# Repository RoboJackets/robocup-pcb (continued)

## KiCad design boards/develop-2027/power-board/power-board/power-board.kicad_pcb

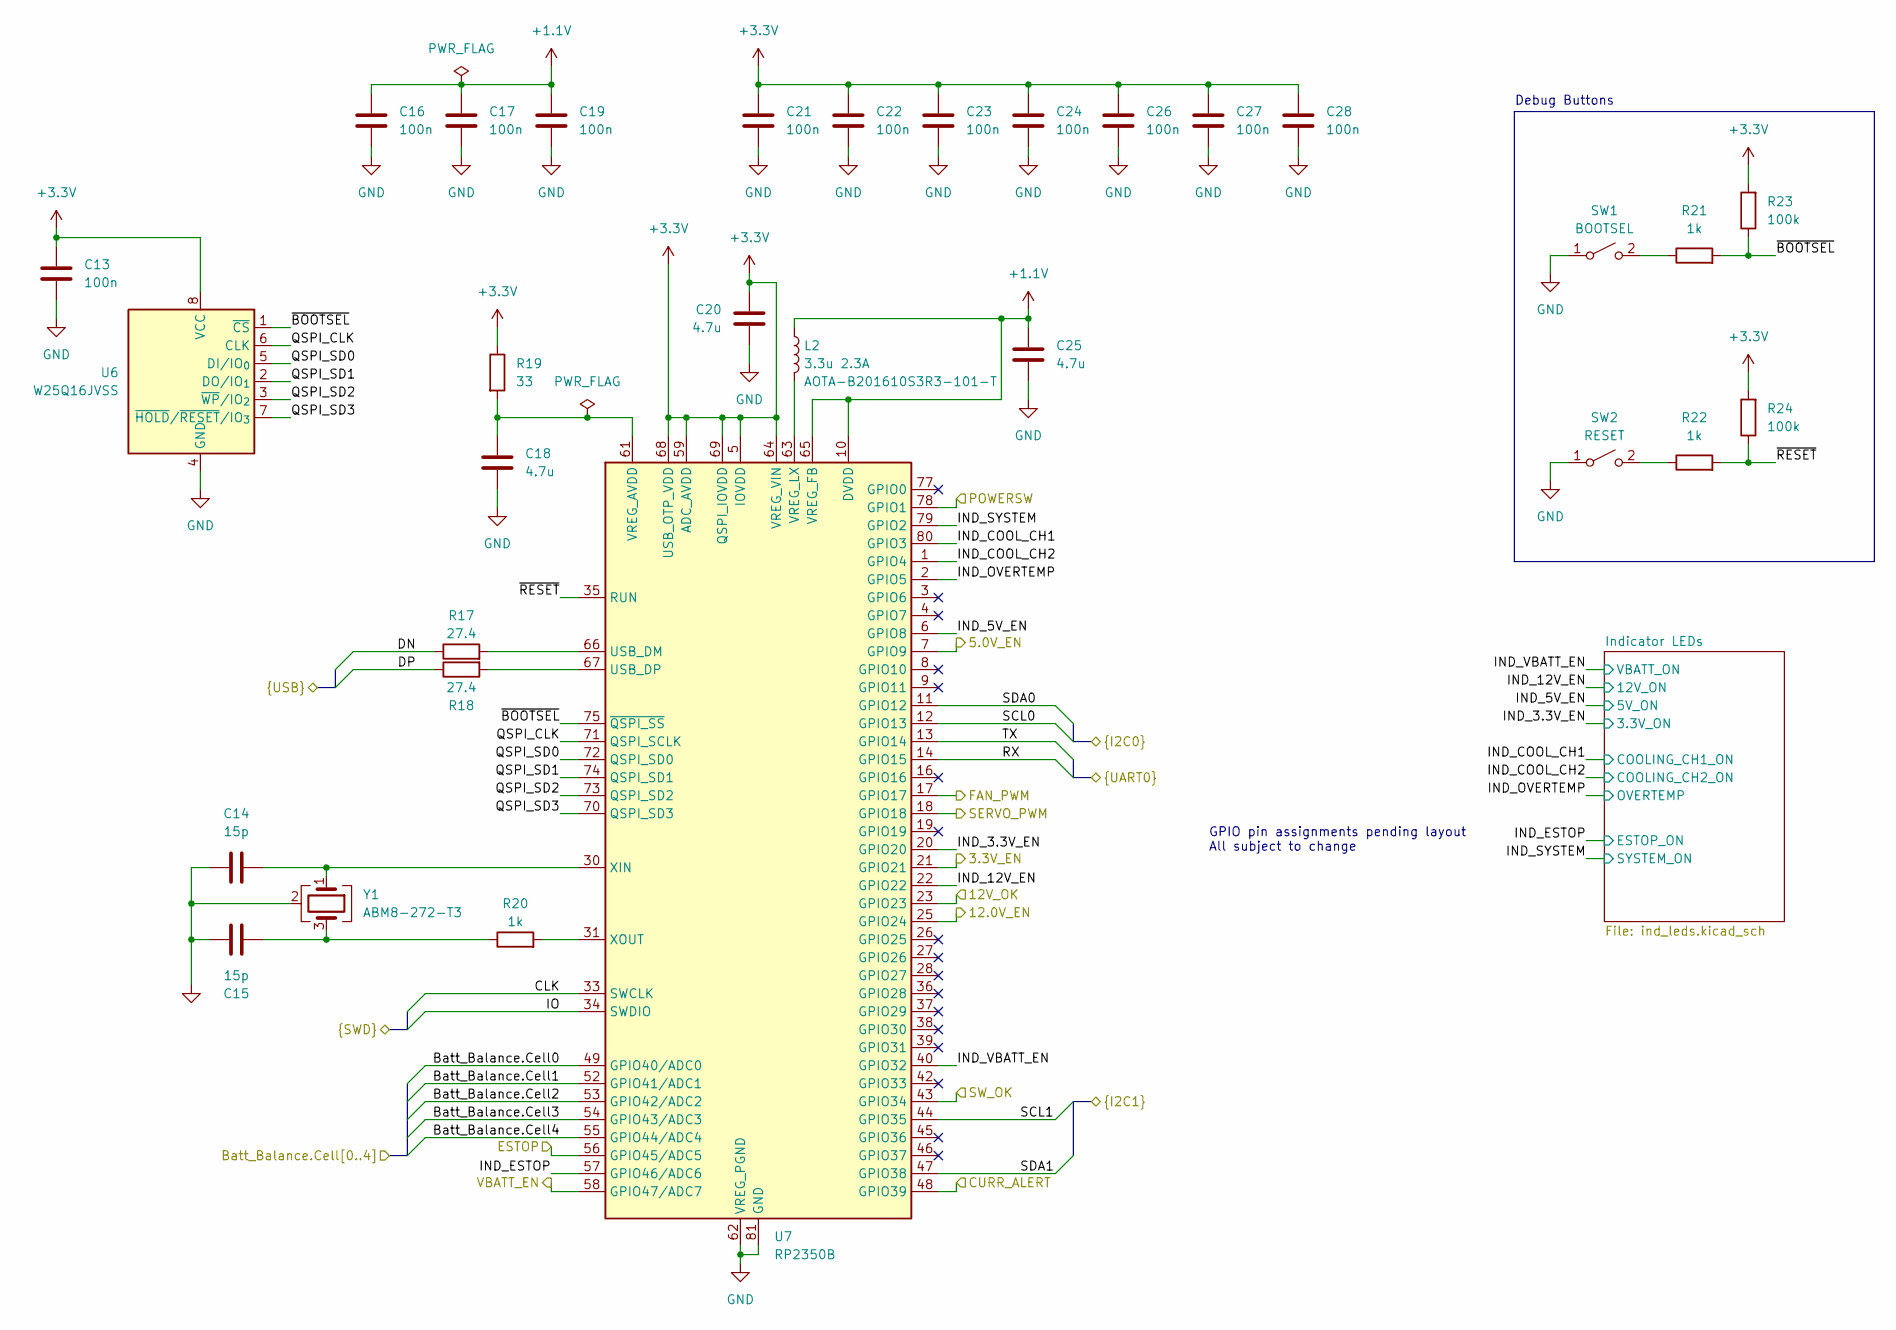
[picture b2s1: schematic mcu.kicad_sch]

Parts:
C13, C16, C17, C19, C21, C22, C23, C24, C26, C27, C28: 100n; C_0402_1005Metric; Manufacturer P/N GCM155R71H104KE02D
C14, C15: 15p; C_0402_1005Metric; Manufacturer P/N GJM1555C1H150GB01D
C18, C20, C25: 4.7u; C_0402_1005Metric; Manufacturer P/N GRM155R60J475ME47D
L2: 3.3u 2.3A; L_Abracon_AOTA-B201610S; Manufacturer P/N AOTA-B201610S3R3-101-T
R17, R18: 27.4; R_0402_1005Metric; Manufacturer P/N RC0402FR-0727R4L
R19: 33; R_0402_1005Metric; Manufacturer P/N RC0402JR-0733RL
R20, R21, R22: 1k; R_0402_1005Metric; Manufacturer P/N RC0402FR-071KL
R23, R24: 100k; R_0402_1005Metric; Manufacturer P/N RC0402FR-07100KL
SW1: BOOTSEL; SW_Push_1P1T_NO_CK_KMR2; Manufacturer P/N KMR211G LFS
SW2: RESET; SW_Push_1P1T_NO_CK_KMR2; Manufacturer P/N KMR211G LFS
U6: W25Q16JVSS; SOIC-8_5.3x5.3mm_P1.27mm; Manufacturer P/N W25Q16JVSSIQ
U7: RP2350B; QFN-80-1EP_10x10mm_P0.4mm_EP3.4x3.4mm; Manufacturer P/N RP2350B
Y1: ABM8-272-T3; Crystal_SMD_Abracon_ABM8G-4Pin_3.2x2.5mm; Manufacturer P/N ABM8-272-T3

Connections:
+1.1V: C16.1, C17.1, C19.1, C25.1, L2.1, U7.10 (DVDD), U7.32 (DVDD), U7.51 (DVDD), U7.65 (VREG_FB)
+3.3V: C13.1, C20.1, C21.1, C22.1, C23.1, C24.1, C26.1, C27.1, C28.1, R19.1, R23.2, R24.2, U6.8 (VCC), U7.5 (IOVDD), U7.15 (IOVDD), U7.24 (IOVDD), U7.29 (IOVDD), U7.41 (IOVDD), U7.50 (IOVDD), U7.59 (ADC_AVDD), U7.60 (IOVDD), U7.64 (VREG_VIN), U7.68 (USB_OTP_VDD), U7.69 (QSPI_IOVDD), U7.76 (IOVDD); also elsewhere on the board
/Battery Connectors/Batt_Balance.Cell0: U7.49 (GPIO40/ADC0); also elsewhere on the board
/Battery Connectors/Batt_Balance.Cell1: U7.52 (GPIO41/ADC1); also elsewhere on the board
/Battery Connectors/Batt_Balance.Cell2: U7.53 (GPIO42/ADC2); also elsewhere on the board
/Battery Connectors/Batt_Balance.Cell3: U7.54 (GPIO43/ADC3); also elsewhere on the board
/Battery Connectors/Batt_Balance.Cell4: U7.55 (GPIO44/ADC4); also elsewhere on the board
/MCU Connectors/CLK: U7.33 (SWCLK); also elsewhere on the board
/MCU Connectors/DN: R17.1; also elsewhere on the board
/MCU Connectors/DP: R18.1; also elsewhere on the board
/MCU Connectors/IO: U7.34 (SWDIO); also elsewhere on the board
/MCU/3.3V_EN: U7.21 (GPIO21); also elsewhere on the board
/MCU/5.0V_EN: U7.7 (GPIO9); also elsewhere on the board
/MCU/12.0V_EN: U7.25 (GPIO24); also elsewhere on the board
/MCU/12V_OK: U7.23 (GPIO23); also elsewhere on the board
/MCU/CURR_ALERT: U7.48 (GPIO39); also elsewhere on the board
/MCU/ESTOP: U7.56 (GPIO45/ADC5); also elsewhere on the board
/MCU/FAN_PWM: U7.17 (GPIO17); also elsewhere on the board
/MCU/IND_3.3V_EN: U7.20 (GPIO20); also elsewhere on the board
/MCU/IND_5V_EN: U7.6 (GPIO8); also elsewhere on the board
/MCU/IND_12V_EN: U7.22 (GPIO22); also elsewhere on the board
/MCU/IND_COOL_CH1: U7.80 (GPIO3); also elsewhere on the board
/MCU/IND_COOL_CH2: U7.1 (GPIO4); also elsewhere on the board
/MCU/IND_ESTOP: U7.57 (GPIO46/ADC6); also elsewhere on the board
/MCU/IND_OVERTEMP: U7.2 (GPIO5); also elsewhere on the board
/MCU/IND_SYSTEM: U7.79 (GPIO2); also elsewhere on the board
/MCU/IND_VBATT_EN: U7.40 (GPIO32); also elsewhere on the board
/MCU/POWERSW: U7.78 (GPIO1); also elsewhere on the board
/MCU/QSPI_CLK: U6.6 (CLK), U7.71 (QSPI_SCLK)
/MCU/QSPI_SD0: U6.5 (DI/IO_{0}), U7.72 (QSPI_SD0)
/MCU/QSPI_SD1: U6.2 (DO/IO_{1}), U7.74 (QSPI_SD1)
/MCU/QSPI_SD2: U6.3 (~WP/IO_{2}), U7.73 (QSPI_SD2)
/MCU/QSPI_SD3: U6.7 (~HOLD/~RESET/IO_{3}), U7.70 (QSPI_SD3)
/MCU/RX: U7.14 (GPIO15); also elsewhere on the board
/MCU/SCL0: U7.12 (GPIO13); also elsewhere on the board
/MCU/SCL1: U7.44 (GPIO35); also elsewhere on the board
/MCU/SDA0: U7.11 (GPIO12); also elsewhere on the board
/MCU/SDA1: U7.47 (GPIO38); also elsewhere on the board
/MCU/SERVO_PWM: U7.18 (GPIO18); also elsewhere on the board
/MCU/SW_OK: U7.43 (GPIO34); also elsewhere on the board
/MCU/TX: U7.13 (GPIO14); also elsewhere on the board
/MCU/VBATT_EN: U7.58 (GPIO47/ADC7); also elsewhere on the board
/MCU/~BOOTSEL: R21.2, R23.1, U6.1 (~CS), U7.75 (~QSPI_SS)
/MCU/~RESET: R22.2, R24.1, U7.35 (RUN)
GND: C13.2, C14.1, C15.1, C16.2, C17.2, C18.2, C19.2, C20.2, C21.2, C22.2, C23.2, C24.2, C25.2, C26.2, C27.2, C28.2, SW1.1 (A), SW2.1 (A), U6.4 (GND), U7.62 (VREG_PGND), U7.81 (GND), Y1.2 (G), Y1.4 (G); also elsewhere on the board
unnamed: C15.2, R20.1, Y1.3
unnamed: R21.1, SW1.2 (B)
unnamed: R22.1, SW2.2 (B)
unnamed: R17.2, U7.66 (USB_DM)
unnamed: R18.2, U7.67 (USB_DP)
unnamed: C18.1, R19.2, U7.61 (VREG_AVDD)
unnamed: L2.2, U7.63 (VREG_LX)
unnamed: C14.2, U7.30 (XIN), Y1.1
unnamed: R20.2, U7.31 (XOUT)

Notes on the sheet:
GPIO pin assignments pending layout All subject to change
Debug Buttons

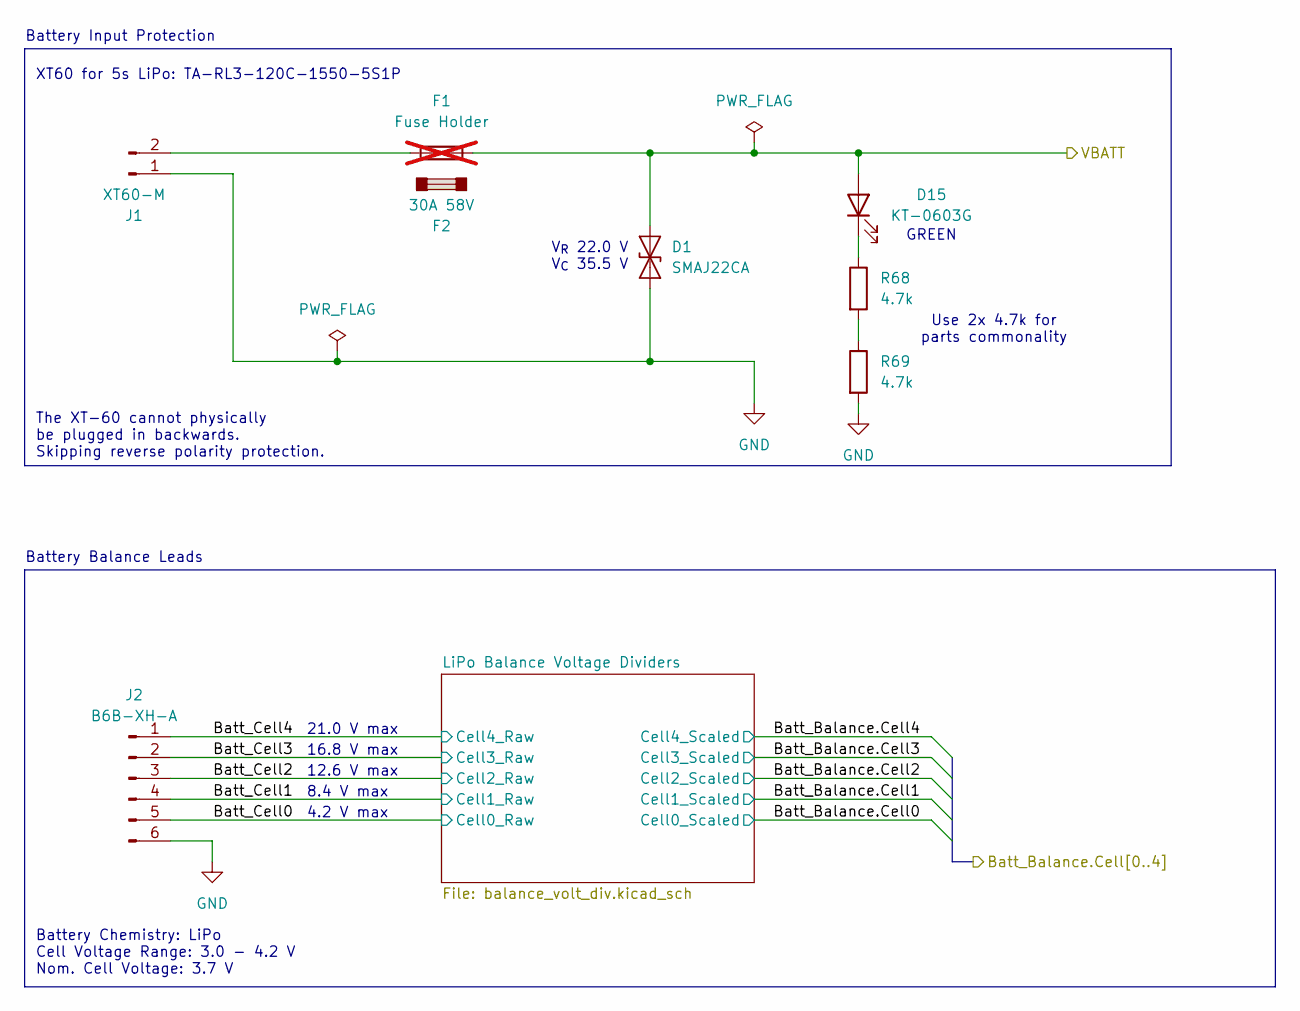
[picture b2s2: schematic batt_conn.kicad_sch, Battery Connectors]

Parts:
D1: SMAJ22CA; D_SMA; Manufacturer P/N SMAJ22CA
D15: KT-0603G; LED_0603_1608Metric; Manufacturer P/N KT-0603G
F1: Fuse Holder; Fuseholder_Keystone_3557-2; Manufacturer P/N 3557-2; not fitted
F2: 30A 58V; Manufacturer P/N 0891030.NXS
J1: XT60-M; AMASS_XT60-M_1x02_P7.20mm_Vertical; Manufacturer P/N XT60-M.
J2: B6B-XH-A; JST_XH_B6B-XH-A_1x06_P2.50mm_Vertical; Manufacturer P/N B6B-XH-A
R68, R69: 4.7k; R_0402_1005Metric; Manufacturer P/N RC0402FR-074K7L

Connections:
/Battery Connectors/Batt_Cell0: J2.5; also elsewhere on the board
/Battery Connectors/Batt_Cell1: J2.4; also elsewhere on the board
/Battery Connectors/Batt_Cell2: J2.3; also elsewhere on the board
/Battery Connectors/Batt_Cell3: J2.2; also elsewhere on the board
/Battery Connectors/Batt_Cell4: J2.1; also elsewhere on the board
/Battery Connectors/VBATT: D1.1 (A1), D15.2 (A), F1.2; also elsewhere on the board
GND: D1.2 (A2), J1.1, J2.6, R69.2; also elsewhere on the board
unnamed: D15.1 (K), R68.1
unnamed: F1.1, J1.2
unnamed: R68.2, R69.1

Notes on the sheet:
4.2 V max
Battery Balance Leads
21.0 V max
Use 2x 4.7k for parts commonality
XT60 for 5s LiPo: TA-RL3-120C-1550-5S1P
12.6 V max
V_{R} 22.0 V V_{C} 35.5 V
8.4 V max
16.8 V max
GREEN
The XT-60 cannot physically be plugged in backwards. Skipping reverse polarity protection.
Battery Input Protection
Battery Chemistry: LiPo Cell Voltage Range: 3.0 - 4.2 V Nom. Cell Voltage: 3.7 V

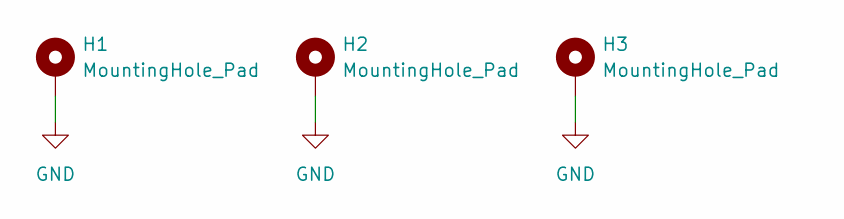
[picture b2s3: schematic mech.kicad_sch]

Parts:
H1, H2, H3: MountingHole_Pad; MountingHole_3.2mm_M3_Pad

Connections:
GND: H1.1 (1_1), H2.1 (1_1), H3.1 (1_1); also elsewhere on the board

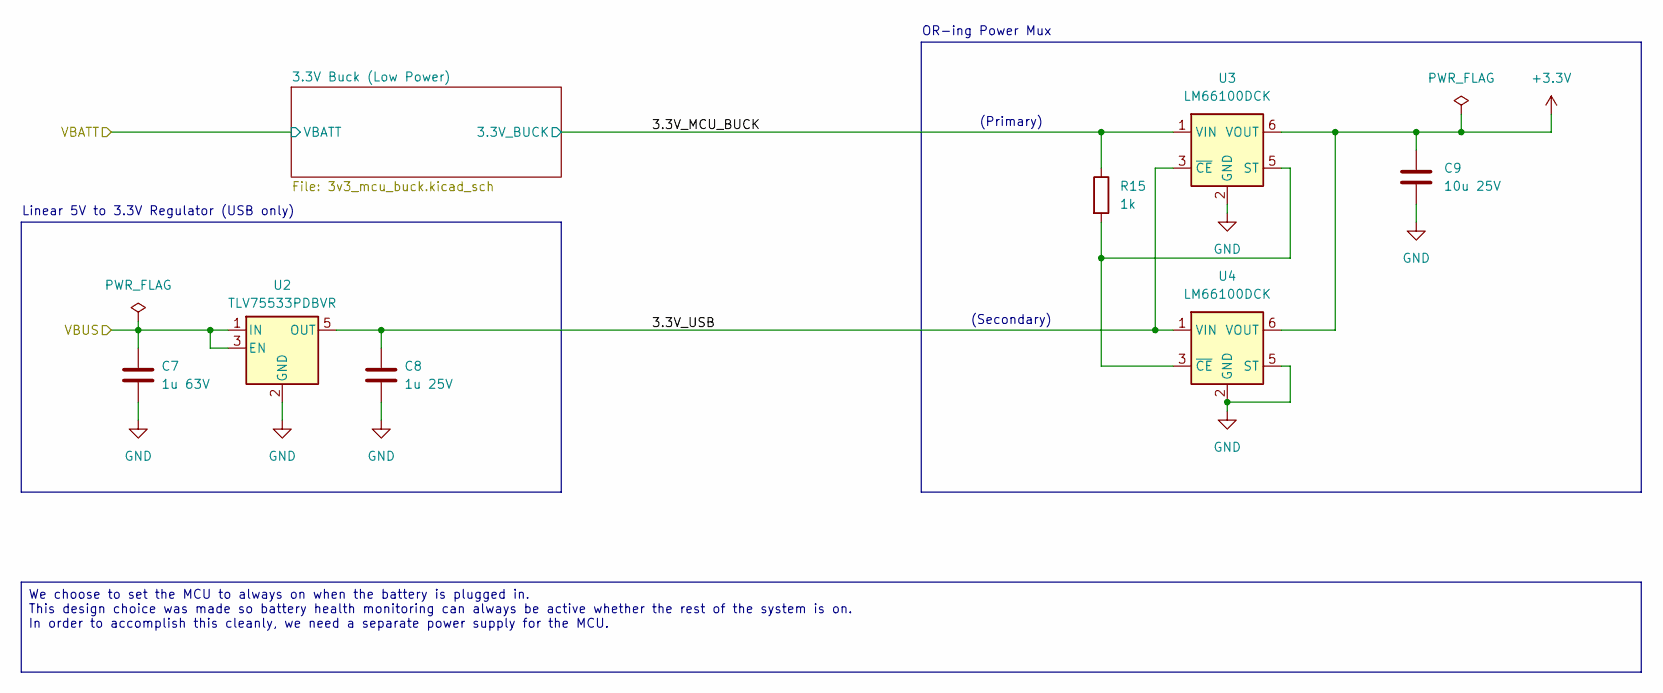
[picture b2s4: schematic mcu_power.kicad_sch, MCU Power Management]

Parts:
C7: 1u 63V; C_0603_1608Metric; Manufacturer P/N CL10B105KB8NQNC
C8: 1u 25V; C_0603_1608Metric; Manufacturer P/N CL10B105KB8NQNC
C9: 10u 25V; C_0603_1608Metric; Manufacturer P/N GRM188R6YA106MA73D
R15: 1k; R_0402_1005Metric; Manufacturer P/N RC0402FR-071KL
U2: TLV75533PDBVR; SOT-23-5; Manufacturer P/N TLV75533PDBVR
U3, U4: LM66100DCK; SOT-363_SC-70-6; Manufacturer P/N LM66100DCKR

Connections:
+3.3V: C9.1, U3.6 (VOUT), U4.6 (VOUT); also elsewhere on the board
/MCU Power/3.3V_MCU_BUCK: R15.1, U3.1 (VIN); also elsewhere on the board
/MCU Power/3.3V_USB: C8.1, U2.5 (OUT), U3.3 (~CE), U4.1 (VIN)
GND: C7.2, C8.2, C9.2, U2.2 (GND), U3.2 (GND), U4.2 (GND), U4.5 (ST); also elsewhere on the board
unnamed: R15.2, U3.5 (ST), U4.3 (~CE)
VBUS: C7.1, U2.1 (IN), U2.3 (EN); also elsewhere on the board

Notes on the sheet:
(Primary)
(Secondary)
Linear 5V to 3.3V Regulator (USB only)
OR-ing Power Mux
We choose to set the MCU to always on when the battery is plugged in. This design choice was made so battery health monitoring can always be active whether the rest of the system is on. In order to accomplish this cleanly, we need a separate power supply for the MCU.

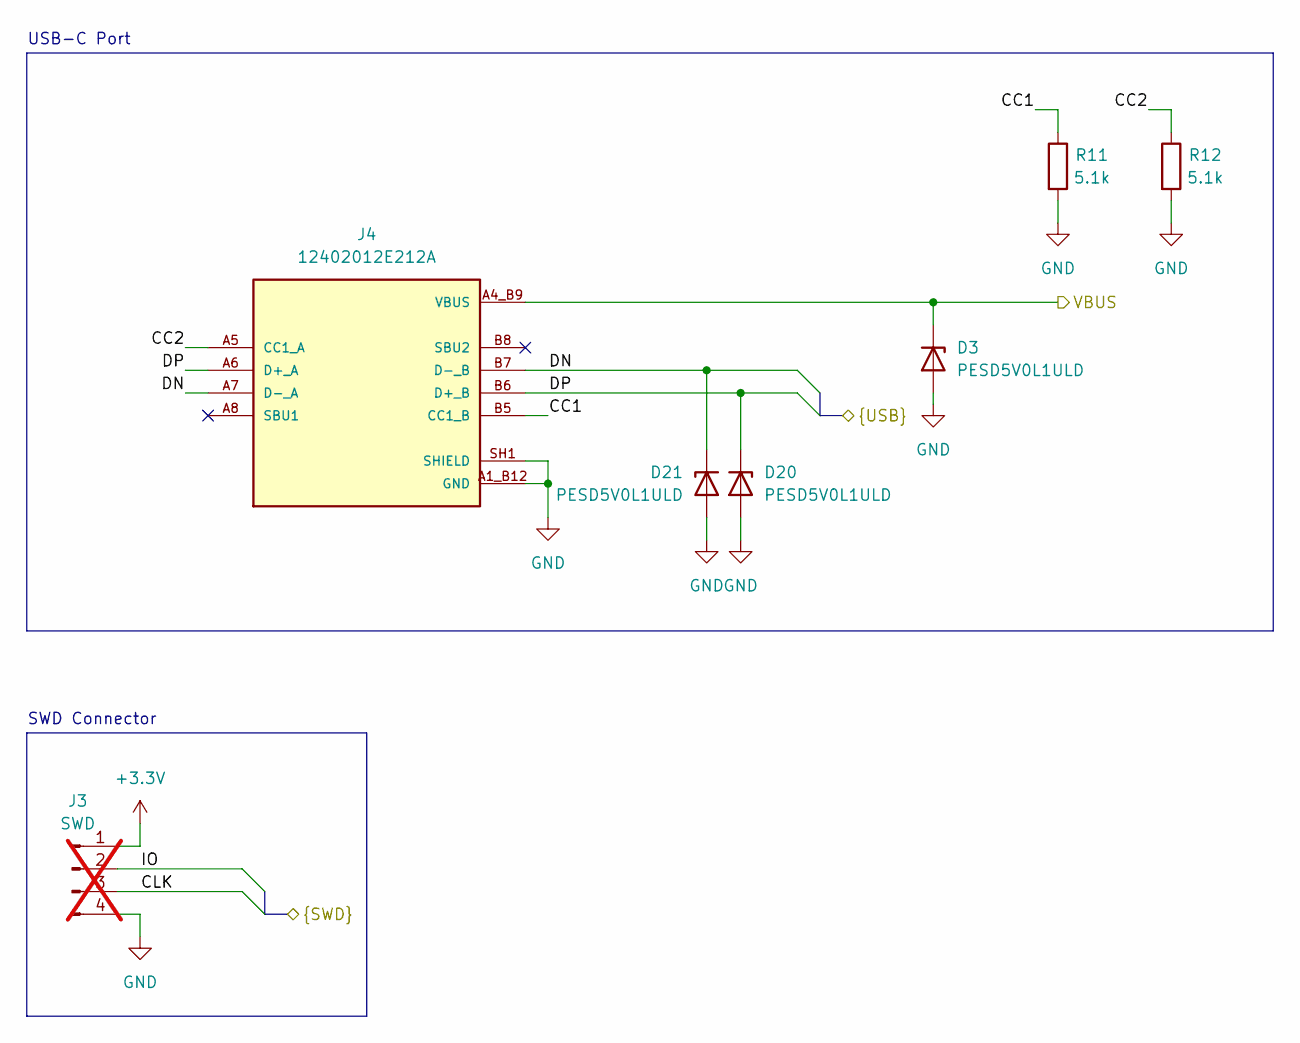
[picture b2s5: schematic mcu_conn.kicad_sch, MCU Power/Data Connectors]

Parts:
D3, D20, D21: PESD5V0L1ULD; D_SOD-882D; Manufacturer P/N PESD5V0H1BSFYL
J3: SWD; PinHeader_1x04_P2.54mm_Vertical; not fitted
J4: 12402012E212A; USB_C_Receptable_Amphenol_12402012E212A; Manufacturer P/N 12402012E212A
R11, R12: 5.1k; R_0402_1005Metric; Manufacturer P/N RC0402FR-075K1L

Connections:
+3.3V: J3.1; also elsewhere on the board
/MCU Connectors/CC1: J4.B5 (CC1_B), R11.1
/MCU Connectors/CC2: J4.A5 (CC1_A), R12.1
/MCU Connectors/CLK: J3.3; also elsewhere on the board
/MCU Connectors/DN: D21.1 (K), J4.A7 (D-_A), J4.B7 (D-_B); also elsewhere on the board
/MCU Connectors/DP: D20.1 (K), J4.A6 (D+_A), J4.B6 (D+_B); also elsewhere on the board
/MCU Connectors/IO: J3.2; also elsewhere on the board
GND: D3.2 (A), D20.2 (A), D21.2 (A), J3.4, J4.A1_B12 (GND), J4.B1_A12 (GND), J4.SH1 (SHIELD), J4.SH2 (SHIELD), J4.SH3 (SHIELD), J4.SH4 (SHIELD), R11.2, R12.2; also elsewhere on the board
VBUS: D3.1 (K), J4.A4_B9 (VBUS), J4.B4_A9 (VBUS); also elsewhere on the board

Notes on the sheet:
SWD Connector
USB-C Port

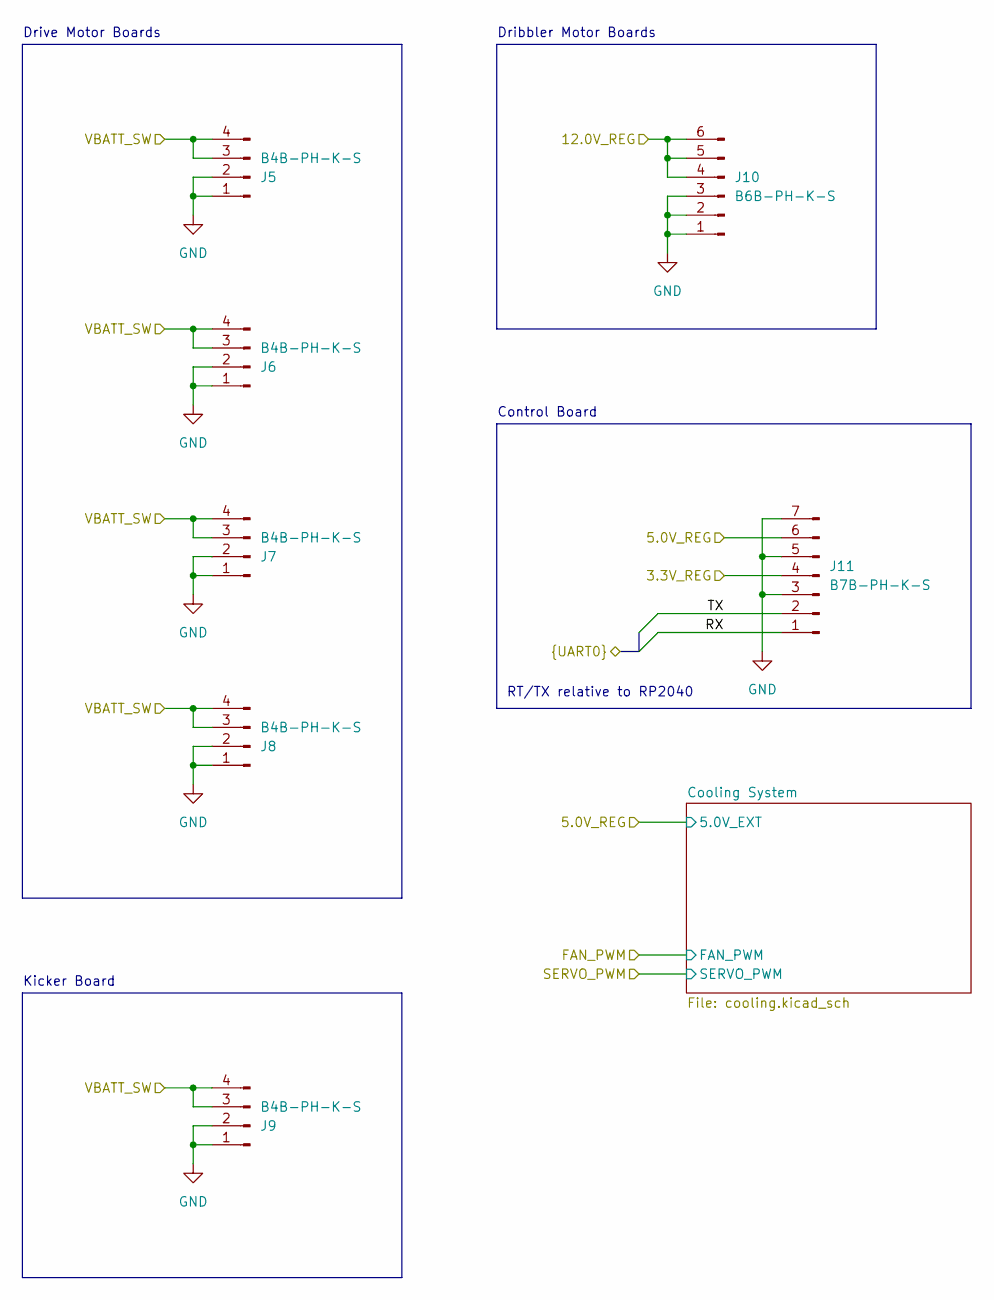
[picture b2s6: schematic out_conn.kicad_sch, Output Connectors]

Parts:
J5, J6, J7, J8, J9: B4B-PH-K-S; JST_PH_B4B-PH-K_1x04_P2.00mm_Vertical; Manufacturer P/N B4B-PH-K-S
J10: B6B-PH-K-S; JST_PH_B6B-PH-K_1x06_P2.00mm_Vertical; Manufacturer P/N B6B-PH-K-S
J11: B7B-PH-K-S; JST_PH_B7B-PH-K_1x07_P2.00mm_Vertical; Manufacturer P/N B7B-PH-K-S

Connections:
/MCU/RX: J11.1; also elsewhere on the board
/MCU/TX: J11.2; also elsewhere on the board
/Output Connectors/3.3V_REG: J11.4; also elsewhere on the board
/Output Connectors/5.0V_REG: J11.6; also elsewhere on the board
/Output Connectors/12.0V_REG: J10.4, J10.5, J10.6; also elsewhere on the board
GND: J5.1, J5.2, J6.1, J6.2, J7.1, J7.2, J8.1, J8.2, J9.1, J9.2, J10.1, J10.2, J10.3, J11.3, J11.5, J11.7; also elsewhere on the board
VIN: J5.3, J5.4, J6.3, J6.4, J7.3, J7.4, J8.3, J8.4, J9.3, J9.4; also elsewhere on the board

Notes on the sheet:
Drive Motor Boards
RT/TX relative to RP2040
Kicker Board
Control Board
Dribbler Motor Boards

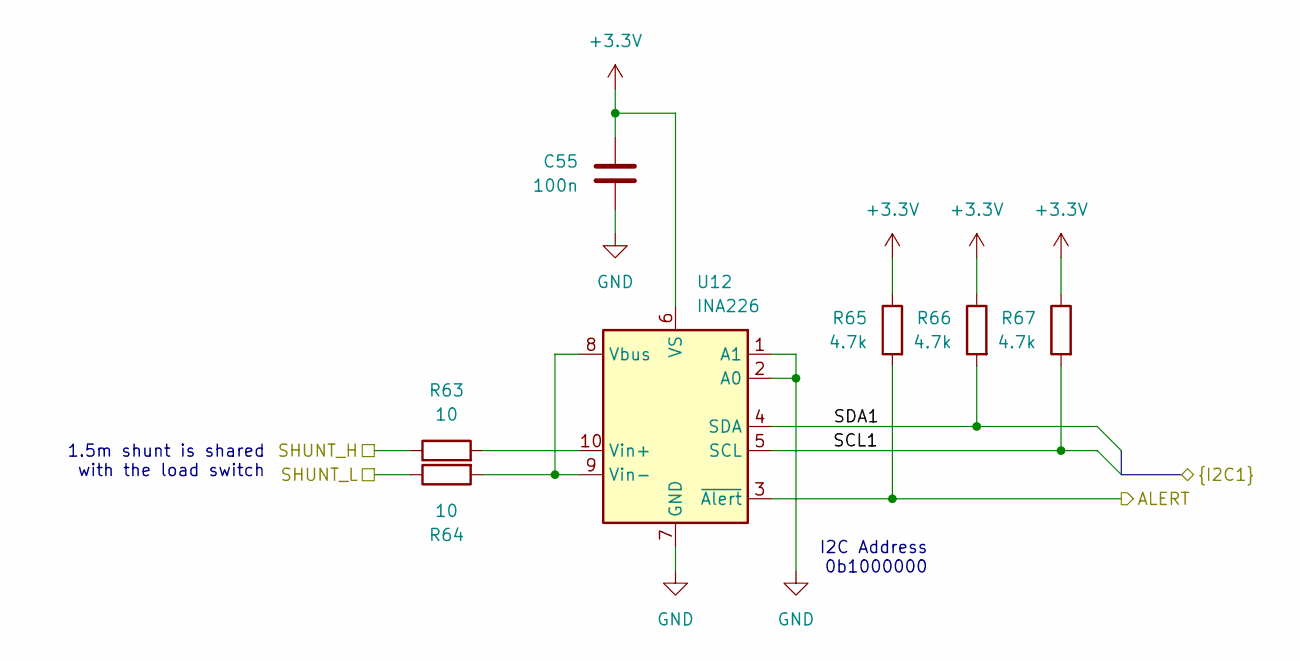
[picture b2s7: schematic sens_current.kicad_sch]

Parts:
C55: 100n; C_0402_1005Metric; Manufacturer P/N GCM155R71H104KE02D
R63, R64: 10; R_0402_1005Metric; Manufacturer P/N RC0402FR-0710RL
R65, R66, R67: 4.7k; R_0402_1005Metric; Manufacturer P/N RC0402FR-074K7L
U12: INA226; TSSOP-10_3x3mm_P0.5mm; Manufacturer P/N INA226AIDGSR

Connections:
+3.3V: C55.1, R65.1, R66.1, R67.1, U12.6 (VS); also elsewhere on the board
/MCU/CURR_ALERT: R65.2, U12.3 (~Alert); also elsewhere on the board
/MCU/SCL1: R67.2, U12.5 (SCL); also elsewhere on the board
/MCU/SDA1: R66.2, U12.4 (SDA); also elsewhere on the board
/Output Power Stage/25V, 30A Load Switch/SHUNT_H: R63.1; also elsewhere on the board
/Output Power Stage/25V, 30A Load Switch/SHUNT_L: R64.1; also elsewhere on the board
GND: C55.2, U12.1 (A1), U12.2 (A0), U12.7 (GND); also elsewhere on the board
unnamed: R64.2, U12.8 (Vbus), U12.9 (Vin-)
unnamed: R63.2, U12.10 (Vin+)

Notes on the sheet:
I2C Address 0b1000000
1.5m shunt is shared with the load switch

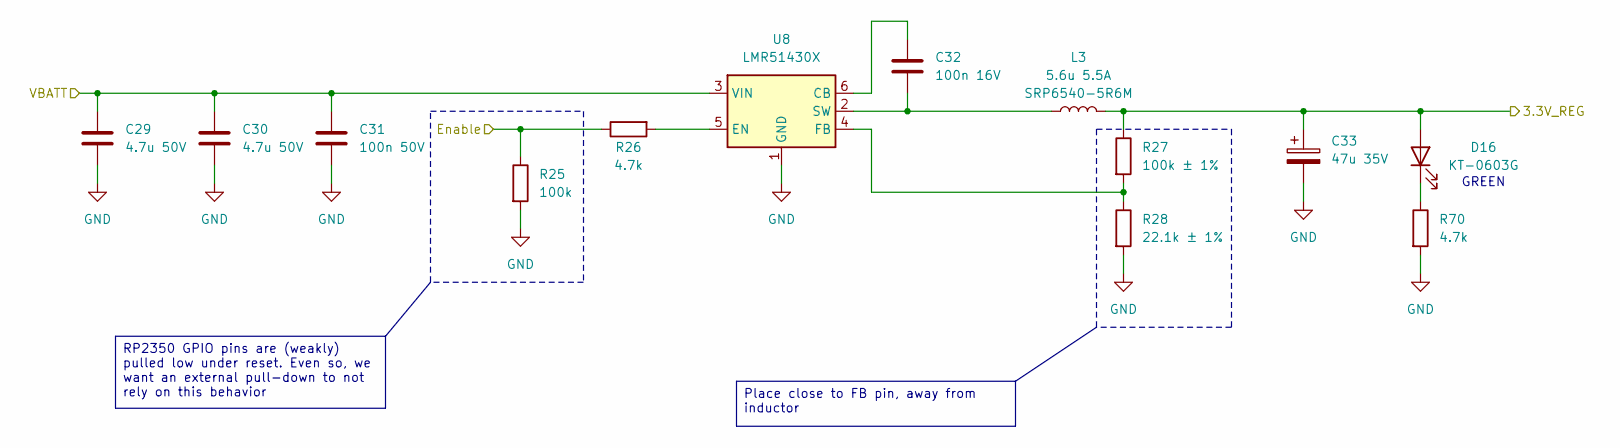
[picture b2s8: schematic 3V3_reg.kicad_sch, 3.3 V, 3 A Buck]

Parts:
C29, C30: 4.7u 50V; C_1206_3216Metric; Manufacturer P/N GRM31CR71H475KA12L
C31: 100n 50V; C_0402_1005Metric; Manufacturer P/N GCM155R71H104KE02D
C32: 100n 16V; C_0402_1005Metric; Manufacturer P/N GCM155R71H104KE02D
C33: 47u 35V; CP_Elec_6.3x5.7; Manufacturer P/N A768EB476M1VLAS042
D16: KT-0603G; LED_0603_1608Metric; Manufacturer P/N KT-0603G
L3: 5.6u 5.5A; L_Bourns_SRP6540; Manufacturer P/N SRP6540-5R6M
R25: 100k; R_0402_1005Metric; Manufacturer P/N RC0402FR-07100KL
R26, R70: 4.7k; R_0402_1005Metric; Manufacturer P/N RC0402FR-074K7L
R27: 100k ± 1%; R_0402_1005Metric; Manufacturer P/N RC0402FR-07100KL
R28: 22.1k ± 1%; R_0402_1005Metric; Manufacturer P/N RMCF0402FT22K1
U8: LMR51430X; SOT-23-6; Manufacturer P/N LMR51430XDDCR

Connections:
/MCU/3.3V_EN: R25.1, R26.1; also elsewhere on the board
/Output Connectors/3.3V_REG: C33.1, D16.2 (A), L3.2, R27.1; also elsewhere on the board
GND: C29.2, C30.2, C31.2, C33.2, R25.2, R28.2, R70.2, U8.1 (GND); also elsewhere on the board
unnamed: D16.1 (K), R70.1
unnamed: C32.1, U8.6 (CB)
unnamed: R26.2, U8.5 (EN)
unnamed: R27.2, R28.1, U8.4 (FB)
unnamed: C32.2, L3.1, U8.2 (SW)
VIN: C29.1, C30.1, C31.1, U8.3 (VIN); also elsewhere on the board

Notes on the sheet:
GREEN
Place close to FB pin, away from inductor
RP2350 GPIO pins are (weakly) pulled low under reset. Even so, we want an external pull-down to not rely on this behavior

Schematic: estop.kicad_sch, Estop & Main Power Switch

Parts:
C52, C53, C54: 100n; C_0402_1005Metric; Manufacturer P/N GCM155R71H104KE02D
R60, R61: 100k; R_0402_1005Metric; Manufacturer P/N RC0402FR-07100KL
R62: 1k; R_0402_1005Metric; Manufacturer P/N RC0402FR-071KL
SW3: TL2201EEYB; SW_E-Switch_TL2201_DPDT; Manufacturer P/N TL2201EEYB; not fitted
SW4: TL1100F160Q6JBLK; SW_PUSH-12mm; Manufacturer P/N TL1100F160Q6JBLK; not fitted

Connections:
+3.3V: SW3.6 (C), SW4.1; also elsewhere on the board
/MCU/ESTOP: C53.1, R60.1, SW3.5 (B); also elsewhere on the board
/MCU/POWERSW: C54.1, R62.2; also elsewhere on the board
/MCU/VBATT_EN: SW3.1 (A); also elsewhere on the board
/Output Power Stage/LOADSW_EN: C52.1, SW3.2 (B); also elsewhere on the board
GND: C52.2, C53.2, C54.2, R60.2, R61.2, SW3.3 (C), SW3.4 (A); also elsewhere on the board
unnamed: R61.1, R62.1, SW4.2

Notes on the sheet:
Optional red key cap: EG1886-ND
2-3, 5-6 connected
Switch ON
Switch OFF
E-Stop Toggle Pushbutton
Driven HIGH when estop is hit
Driven LOW when estop is hit
Main Power Switch
(pulldown already exists downstream)
1-2, 4-5 connected
This button is supposed to trigger the controlled start-up/shut-down sequence that is controlled by the onboard MCU.
This E-stop does two functions: 1. It cuts off the power to the rest of the system by disabing the master load switch 2. Noifies the MCU that an E-Stop event has been triggered through a GPIO signal

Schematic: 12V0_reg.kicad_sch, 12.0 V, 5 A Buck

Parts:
C41, C42: 4.7u 50V; C_1206_3216Metric; Manufacturer P/N GRM31CR71H475KA12L
C43: 100n 50V; C_0402_1005Metric; Manufacturer P/N GCM155R71H104KE02D
C44: 100n 16V; C_0402_1005Metric; Manufacturer P/N GCM155R71H104KE02D
C45: 33p; C_0402_1005Metric; Manufacturer P/N GCM1555C1H330JA16D
C46, C47: 47u 35V; CP_Elec_6.3x5.7; Manufacturer P/N A768EB476M1VLAS042
D18: KT-0603G; LED_0603_1608Metric; Manufacturer P/N KT-0603G
L5: 6.8u 8A; L_Bourns_SRP1038C_10.0x10.0mm; Manufacturer P/N SRP1038A-6R8M
R33, R36: 100k; R_0402_1005Metric; Manufacturer P/N RC0402FR-07100KL
R34, R72: 4.7k; R_0402_1005Metric; Manufacturer P/N RC0402FR-074K7L
R35: 31.6k ± 1%; R_0402_1005Metric; Manufacturer P/N RC0402FR-0731K6L
R37: 100k ± 1%; R_0402_1005Metric; Manufacturer P/N RC0402FR-07100KL
R38: 7.15k ± 1%; R_0402_1005Metric; Manufacturer P/N RC0402FR-077K15L
R39: 1k; R_0402_1005Metric; Manufacturer P/N RC0402FR-071KL
U10: LMR51450; WSON-12-1EP_3x3mm_P0.5mm_EP1.5x2.5mm; Manufacturer P/N LMR51450FNDRRR

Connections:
+3.3V: R36.2; also elsewhere on the board
/MCU/12.0V_EN: R33.1, R34.1; also elsewhere on the board
/MCU/12V_OK: R36.1, U10.5 (PG); also elsewhere on the board
/Output Connectors/12.0V_REG: C46.1, C47.1, D18.2 (A), L5.2, R37.1, R39.1; also elsewhere on the board
GND: C41.2, C42.2, C43.2, C46.2, C47.2, R33.2, R35.2, R38.2, R72.2, U10.8 (AGND), U10.13 (PGND); also elsewhere on the board
unnamed: C44.2, L5.1, U10.1 (SW), U10.2 (SW), U10.3 (SW)
unnamed: C45.1, R39.2
unnamed: D18.1 (K), R72.1
unnamed: C44.1, U10.4 (BOOT)
unnamed: R34.2, U10.9 (EN)
unnamed: C45.2, R37.2, R38.1, U10.7 (FB)
unnamed: R35.1, U10.6 (RT)
VIN: C41.1, C42.1, C43.1, U10.10 (VIN), U10.11 (VIN), U10.12 (VIN); also elsewhere on the board

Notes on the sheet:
LMR51440x are drop-in replacements that lower I_{MAX} from 5A to 4A
GREEN
R_{FBT}
36 V max input
Assume K_{IND} = 0.6
R_{FBB}
RP2350 GPIO pins are (weakly) pulled low under reset. Even so, we want an external pull-down to not rely on this behavior
Section 8.3.4 in LP514x0 datasheet Table 8-1 Pull-down of 31.6R sets F_{SW} = 495 kHz
Section 8.3.2 in LP514x0 datasheet R_{FBT}/R_{FBB} = (V_{OUT} - 0.8 V) / 0.8 V V_{OUT} ≈ 11.98 V Place close to FB pin, away from inductor

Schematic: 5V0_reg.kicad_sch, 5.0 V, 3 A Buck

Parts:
C35, C36: 4.7u 50V; C_1206_3216Metric; Manufacturer P/N GRM31CR71H475KA12L
C37: 100n 50V; C_0402_1005Metric; Manufacturer P/N GCM155R71H104KE02D
C38: 100n 16V; C_0402_1005Metric; Manufacturer P/N GCM155R71H104KE02D
C39: 47u 35V; CP_Elec_6.3x5.7; Manufacturer P/N A768EB476M1VLAS042
D17: KT-0603G; LED_0603_1608Metric; Manufacturer P/N KT-0603G
L4: 6.8u 5A; L_Bourns_SRP6540; Manufacturer P/N SRP6540-6R8M
R29: 100k; R_0402_1005Metric; Manufacturer P/N RC0402FR-07100KL
R30, R71: 4.7k; R_0402_1005Metric; Manufacturer P/N RC0402FR-074K7L
R31: 100k ± 1%; R_0402_1005Metric; Manufacturer P/N RC0402FR-07100KL
R32: 13.7k ± 1%; R_0402_1005Metric; Manufacturer P/N RC0402FR-0713K7L
U9: LMR51430X; SOT-23-6; Manufacturer P/N LMR51430XDDCR

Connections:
/MCU/5.0V_EN: R29.1, R30.1; also elsewhere on the board
/Output Connectors/5.0V_REG: C39.1, D17.2 (A), L4.2, R31.1; also elsewhere on the board
GND: C35.2, C36.2, C37.2, C39.2, R29.2, R32.2, R71.2, U9.1 (GND); also elsewhere on the board
unnamed: D17.1 (K), R71.1
unnamed: C38.1, U9.6 (CB)
unnamed: R30.2, U9.5 (EN)
unnamed: R31.2, R32.1, U9.4 (FB)
unnamed: C38.2, L4.1, U9.2 (SW)
VIN: C35.1, C36.1, C37.1, U9.3 (VIN); also elsewhere on the board

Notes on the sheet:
GREEN
RP2350 GPIO pins are (weakly) pulled low under reset. Even so, we want an external pull-down to not rely on this behavior
Place close to FB pin, away from inductor

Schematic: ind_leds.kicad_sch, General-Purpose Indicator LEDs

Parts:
D5, D6, D7, D8: KT-0603G; LED_0603_1608Metric; Manufacturer P/N KT-0603G
D9, D10, D13: KT-0603O; LED_0603_1608Metric; Manufacturer P/N KT-0603O
D11, D12: KT-0603R; LED_0603_1608Metric; Manufacturer P/N KT-0603R
R48, R49, R50, R51, R52, R53, R54, R55, R56: 1k; R_0402_1005Metric; Manufacturer P/N RC0402FR-071KL

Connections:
/MCU/IND_3.3V_EN: D8.2 (A); also elsewhere on the board
/MCU/IND_5V_EN: D7.2 (A); also elsewhere on the board
/MCU/IND_12V_EN: D6.2 (A); also elsewhere on the board
/MCU/IND_COOL_CH1: D9.2 (A); also elsewhere on the board
/MCU/IND_COOL_CH2: D10.2 (A); also elsewhere on the board
/MCU/IND_ESTOP: D12.2 (A); also elsewhere on the board
/MCU/IND_OVERTEMP: D11.2 (A); also elsewhere on the board
/MCU/IND_SYSTEM: D13.2 (A); also elsewhere on the board
/MCU/IND_VBATT_EN: D5.2 (A); also elsewhere on the board
GND: R48.2, R49.2, R50.2, R51.2, R52.2, R53.2, R54.2, R55.2, R56.2; also elsewhere on the board
unnamed: D5.1 (K), R48.1
unnamed: D6.1 (K), R49.1
unnamed: D7.1 (K), R50.1
unnamed: D8.1 (K), R51.1
unnamed: D9.1 (K), R52.1
unnamed: D10.1 (K), R53.1
unnamed: D11.1 (K), R54.1
unnamed: D12.1 (K), R55.1
unnamed: D13.1 (K), R56.1

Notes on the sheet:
Entire System Indicators
ORANGE
GREEN
RED
Cooling System
Voltage Rail Indicators

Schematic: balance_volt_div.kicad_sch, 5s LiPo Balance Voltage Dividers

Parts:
C1, C2, C3, C4, C5: 100n; C_0402_1005Metric; Manufacturer P/N GCM155R71H104KE02D
R1, R8: 180k ± 0.1%; R_0603_1608Metric; Manufacturer P/N RT0603BRE07180KL
R2, R6, R10: 330k ± 0.1%; R_0603_1608Metric; Manufacturer P/N AT0603BRD07330KL
R3, R7, R9: 1.2M ± 0.1%; R_0603_1608Metric; Manufacturer P/N MCT0603MD1204BP500
R4: 220k ± 0.1%; R_0603_1608Metric; Manufacturer P/N PTFR0603B220KP9
R5: 680k ± 0.1%; R_0603_1608Metric; Manufacturer P/N RT0603BRD07680KL

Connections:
/Battery Connectors/Batt_Balance.Cell0: C1.1, R1.2, R2.1; also elsewhere on the board
/Battery Connectors/Batt_Balance.Cell1: C3.1, R5.2, R6.1; also elsewhere on the board
/Battery Connectors/Batt_Balance.Cell2: C5.1, R9.2, R10.1; also elsewhere on the board
/Battery Connectors/Batt_Balance.Cell3: C2.1, R3.2, R4.1; also elsewhere on the board
/Battery Connectors/Batt_Balance.Cell4: C4.1, R7.2, R8.1; also elsewhere on the board
/Battery Connectors/Batt_Cell0: R1.1; also elsewhere on the board
/Battery Connectors/Batt_Cell1: R5.1; also elsewhere on the board
/Battery Connectors/Batt_Cell2: R9.1; also elsewhere on the board
/Battery Connectors/Batt_Cell3: R3.1; also elsewhere on the board
/Battery Connectors/Batt_Cell4: R7.1; also elsewhere on the board
GND: C1.2, C2.2, C3.2, C4.2, C5.2, R2.2, R4.2, R6.2, R8.2, R10.2; also elsewhere on the board

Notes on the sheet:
Voltage Divider 2 - 12.6 V max
Voltage Divider 1 - 8.4 V max
Voltage Divider 0 - 4.2 V max
Input Range: 0.0 - 4.2 V Divider Ratio: 1.55:1 Final Voltage Range: 0.0 - 2.72 V
Voltage Divider 3 - 16.8 V max
Voltage Divider 0 - 21 V max
Input Range: 0.0 - 12.6 V Divider Ratio: 4.63:1 Final Voltage Range: 0.0 - 2.72 V
Input Range: 0.0 - 8.4 V Divider Ratio: 3.05:1 Final Voltage Range: 0.0 - 2.75 V
Input Range: 0.0 - 21.0 V Divider Ratio: 7.66:1 Final Voltage Range: 0.0 - 2.74 V
Input Range: 0.0 - 16.8 V Divider Ratio: 6.46:1 Final Voltage Range: 0.0 - 2.60 V
The intent of these dividers is to get a general idea of the battery's charge level, rather than get an exact measurement. As such, the decreased resolution caused by scaling down the voltage to 3.3 V max is acceptable. If more precision is needed in the future, consider using op-amps instead.

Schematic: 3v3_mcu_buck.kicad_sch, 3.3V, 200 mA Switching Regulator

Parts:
C10: 1u 63V; C_0603_1608Metric; Manufacturer P/N CL10B105KB8NQNC
C11, C12: 10u 25V; C_0603_1608Metric; Manufacturer P/N GRM188R6YA106MA73D
L1: 10u 540mA; L_1210_3225Metric; Manufacturer P/N LBC3225T100KR
R16: 100k; R_0402_1005Metric; Manufacturer P/N RC0402FR-07100KL
U5: TPS62177DQC; WSON-10-1EP_2x3mm_P0.5mm_EP0.84x2.4mm; Manufacturer P/N TPS62177DQC

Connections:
/Battery Connectors/VBATT: C10.1, U5.2 (VIN), U5.3 (EN); also elsewhere on the board
/MCU Power/3.3V_MCU_BUCK: C11.1, C12.1, L1.2, R16.1, U5.8 (~SLEEP), U5.10 (VOS); also elsewhere on the board
GND: C10.2, C11.2, C12.2, U5.1 (PGND), U5.4 (NC), U5.5 (FB), U5.6 (AGND), U5.11 (PAD); also elsewhere on the board
unnamed: R16.2, U5.7 (PG)
unnamed: L1.1, U5.9 (SW)

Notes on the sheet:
Connect directly to VOUT if possible Regulator always on

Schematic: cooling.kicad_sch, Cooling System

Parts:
D14: SMD110PL-TP; D_SOD-123F; Manufacturer P/N SMD110PL-TP
M1: Motor_Servo; PinHeader_1x03_P2.54mm_Vertical; not fitted
M2: B2B-XH-A; JST_XH_B2B-XH-A_1x02_P2.50mm_Vertical; Manufacturer P/N B2B-XH-A
Q2: AO3400A; SOT-23; Manufacturer P/N AO3400A
R57, R58: 1k; R_0402_1005Metric; Manufacturer P/N RC0402FR-071KL
R59: 100k; R_0402_1005Metric; Manufacturer P/N RC0402FR-07100KL

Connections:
/MCU/FAN_PWM: R57.1; also elsewhere on the board
/MCU/SERVO_PWM: R58.1; also elsewhere on the board
/Output Connectors/5.0V_REG: D14.1 (K), M1.2 (+), M2.1 (+); also elsewhere on the board
GND: M1.3 (-), Q2.2 (S), R59.2; also elsewhere on the board
unnamed: D14.2 (A), M2.2 (-), Q2.3 (D)
unnamed: M1.1 (PWM), R58.2
unnamed: Q2.1 (G), R57.2, R59.1

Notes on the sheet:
Use fan 259-1794-ND
Cooling Fan
Servo Motor
Intended for SG90 "blue" servo motor
